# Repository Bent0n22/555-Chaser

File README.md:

# 555-Chaser
This is my first HackClub project. It is an LED Chaser PCB heart to give my girlfriend.

I decided to make this proejct after my friend introduced me to hackclub!

All files are above!

| Bill of Materials |
|-------------------|

| Name | Purpose | Qty | Total (USD) | Link	| Distributor |
| ---- | ------- | --- | ----------- | ---- | ----------- |
|Blinky Board Kit | Shipped to you - kit project	| 1	| $10.00 | - | Hack Club |
| Custom PCB	| The Board part of my Blinky Board. Makes everything work. |	1 |	$2.00 |	[Link](https://cart.jlcpcb.com/quote?stencilLayer=2&stencilWidth=100&stencilLength=100&stencilCounts=5&plateType=1&spm=Jlcpcb.Homepage.1010)	| JLCPCB |

| Shipping: $3.30 | Total Cost: $15.30 |
| --------------- | ------------------ |

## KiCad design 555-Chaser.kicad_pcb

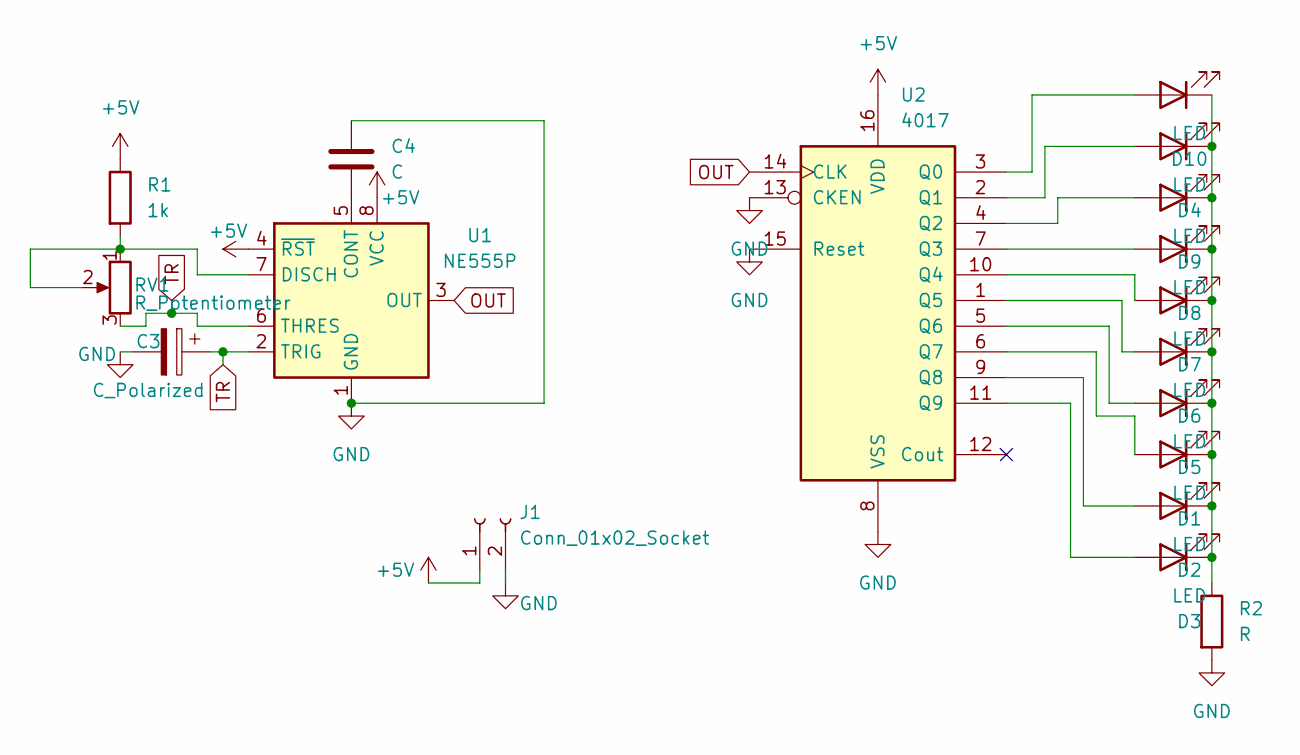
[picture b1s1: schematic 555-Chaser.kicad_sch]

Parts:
C3: C_Polarized; CP_Radial_D5.0mm_P2.00mm
C4: C; C_Disc_D7.5mm_W2.5mm_P5.00mm
D1, D2, D3, D4, D5, D6, D7, D8, D9, D10: LED; LED_D3.0mm
J1: Conn_01x02_Socket; PinHeader_1x02_P2.54mm_Vertical
R1: 1k; R_Axial_DIN0207_L6.3mm_D2.5mm_P7.62mm_Horizontal
R2: R; R_Axial_DIN0207_L6.3mm_D2.5mm_P7.62mm_Horizontal
RV1: R_Potentiometer; Potentiometer_Vishay_T93YA_Vertical
U1: NE555P; DIP-8_W7.62mm
U2: 4017; N16

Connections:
+5V: J1.1, R1.1, U1.4 (~RST), U1.8 (VCC), U2.16 (VDD)
GND: C3.2, C4.1, J1.2, R2.2, U1.1 (GND), U2.8 (VSS), U2.13 (CKEN), U2.15 (Reset)
unnamed: D1.2 (A), U2.6 (Q7)
unnamed: D1.1 (K), D2.1 (K), D3.1 (K), D4.1 (K), D5.1 (K), D6.1 (K), D7.1 (K), D8.1 (K), D9.1 (K), D10.1 (K), R2.1
unnamed: D2.2 (A), U2.9 (Q8)
unnamed: D3.2 (A), U2.11 (Q9)
unnamed: D4.2 (A), U2.2 (Q1)
unnamed: D5.2 (A), U2.5 (Q6)
unnamed: D6.2 (A), U2.1 (Q5)
unnamed: D7.2 (A), U2.10 (Q4)
unnamed: D8.2 (A), U2.7 (Q3)
unnamed: D9.2 (A), U2.4 (Q2)
unnamed: D10.2 (A), U2.3 (Q0)
unnamed: C4.2, U1.5 (CONT)
unnamed: R1.2, RV1.1, RV1.2, U1.7 (DISCH)
OUT: U1.3 (OUT), U2.14 (CLK)
TR: C3.1, RV1.3, U1.2 (TRIG), U1.6 (THRES)

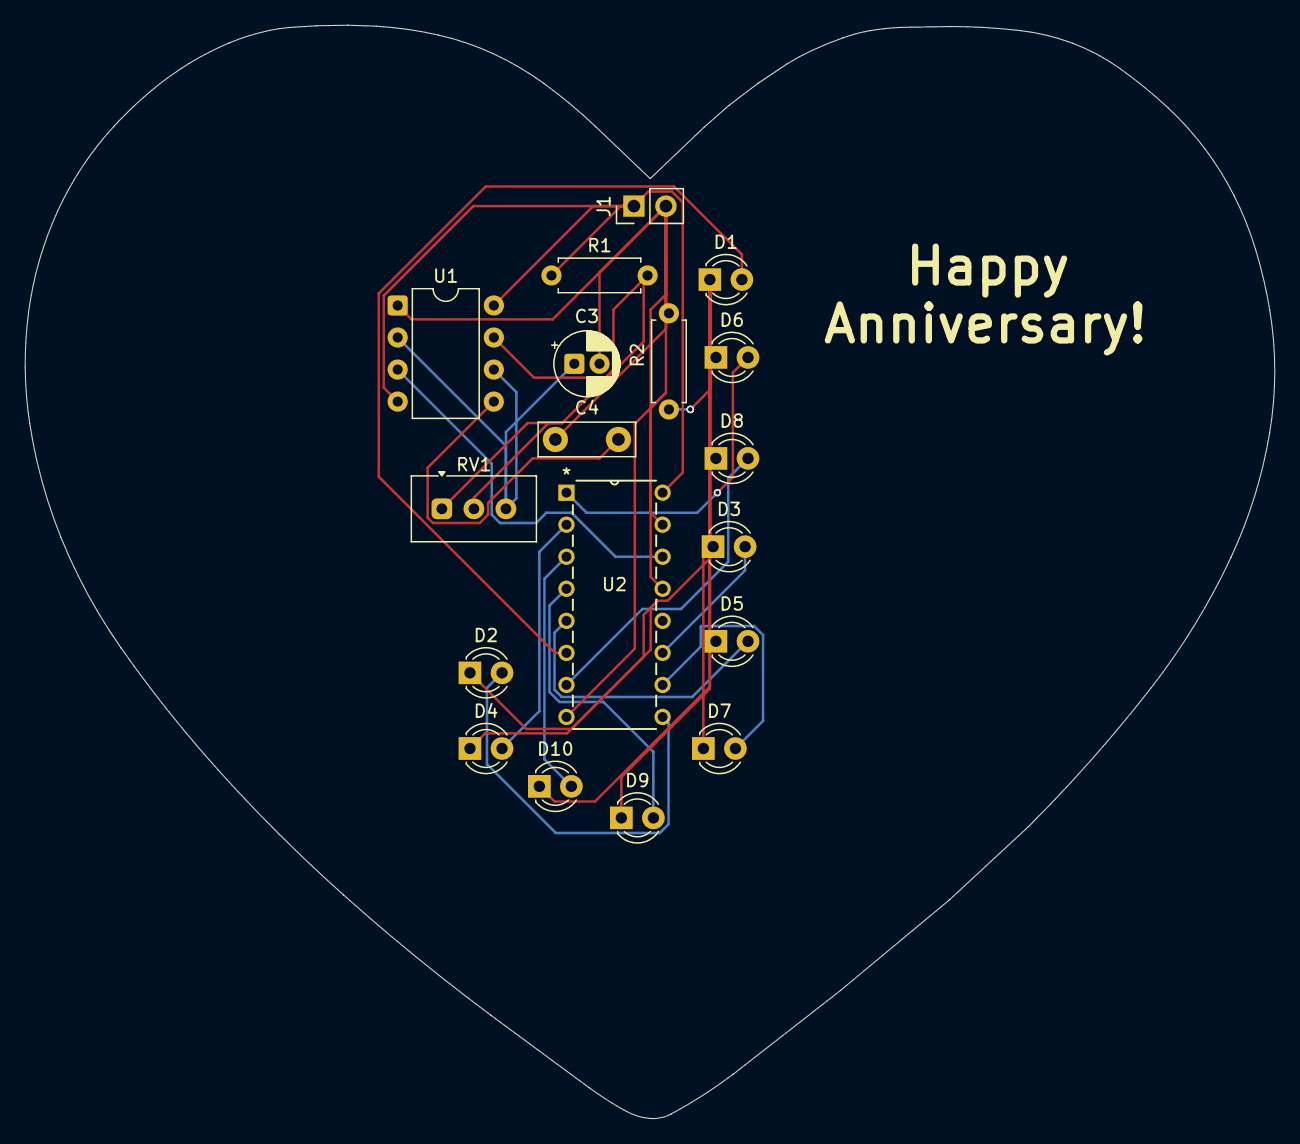
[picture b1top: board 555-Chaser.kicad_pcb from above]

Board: 2 copper layers, 99.1 x 86.7 mm, 18 parts (0 on the bottom side), 17 nets.

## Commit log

2026-05-05 README.md
